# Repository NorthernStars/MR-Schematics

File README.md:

MR-Schematics
============

This repository includes schematic and pcb layout files for some electronical hardware of the Mixed-Reality system.
Cadsoft Eagle (http://www.cadsoftusa.com/?lang=en) is used to generate the these files. Sometimes also a partlist is included.

Included Files
-----
This repository includes files for the following hardware:
* mrShark - Robot mrShark including programmer and debug/charger boards
* IR Testboard - Board for redirecting serial and IR data for debugging
* IR Transmitter - USB Infrared transmitter
* IR Splitter - Splitter for IR system with high current
* LiPo-Charger MultiBoard - Small Robot LiPo chargers that are connectable to any size of charger station
* LiPo-Charger-Station - 3x3 Robot LiPo charger station with microcontroller

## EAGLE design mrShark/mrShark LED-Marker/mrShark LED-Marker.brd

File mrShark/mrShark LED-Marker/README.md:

# mrShark LED-Marker
LEd marker for Mixed-Reality Robotr mrShark.
Includes 3x3 led arry an 4 position lights.
Controlled via I2C/TWI PC9552 led controller.

## PCB Order
Order on 

https://jlcpcb.com/

and upload Gerber File zip.
Dimension of pcb is 26mm x 32mm
    
## Assembly
Place LEDs, ICs and R1, R2, R3 as shown in schematics.
Choose R4 - R11 and R21 corresponding to your LED current (volatge of mrShark is max. 4.1V, average 3.0 - 3.3V, min 2.7V).
Choose R12, R13 for two! LEDs.

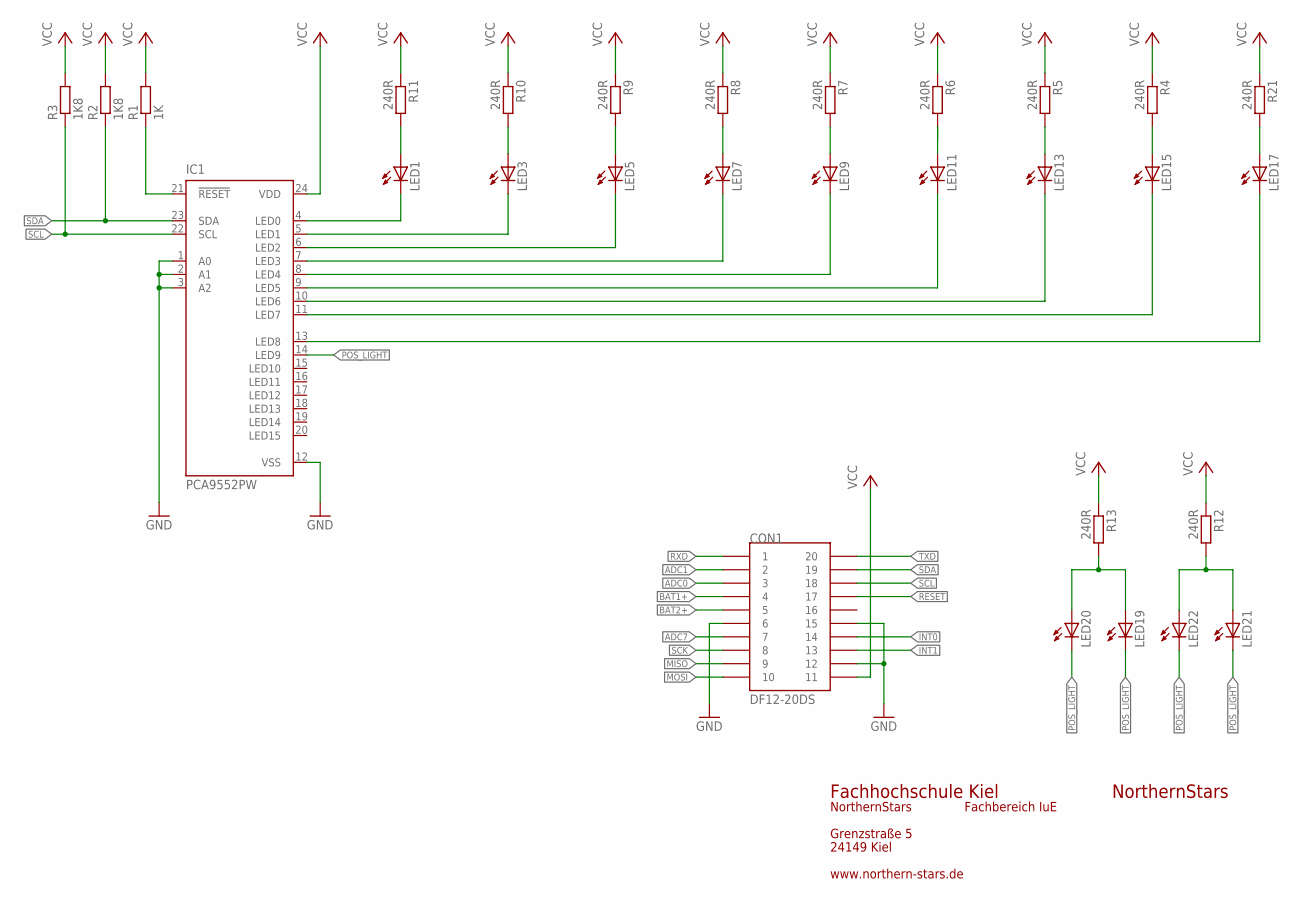
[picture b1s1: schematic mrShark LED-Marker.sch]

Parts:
CON1: DF12-20DS
IC1: PCA9552PW; TSSOP24
LED1, LED3, LED5, LED7, LED9, LED11, LED13, LED15, LED17, LED19, LED20, LED21, LED22: LEDCHIPLED_0603; CHIPLED_0603
R1: 1K; R0603
R2, R3: 1K8; R0603
R4, R5, R6, R7, R8, R9, R10, R11, R12, R13, R21: 240R; R0603

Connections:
ADC0: CON1.3
ADC1: CON1.2
ADC7: CON1.7
BAT1+: CON1.4
BAT2+: CON1.5
GND: CON1.6, CON1.12, CON1.15, IC1.1 (A0), IC1.2 (A1), IC1.3 (A2), IC1.12 (VSS)
INT0: CON1.14
INT1: CON1.13
MISO: CON1.9
MOSI: CON1.10
unnamed: IC1.21 (!RESET), R1.1
unnamed: LED17.A, R21.2
unnamed: LED21.A, LED22.A, R12.2
unnamed: LED15.A, R4.2
unnamed: LED13.A, R5.2
unnamed: LED11.A, R6.2
unnamed: LED9.A, R7.2
unnamed: LED7.A, R8.2
unnamed: LED19.A, LED20.A, R13.2
unnamed: LED5.A, R9.2
unnamed: LED3.A, R10.2
unnamed: LED1.A, R11.2
unnamed: IC1.4 (LED0), LED1.C
unnamed: IC1.5 (LED1), LED3.C
unnamed: IC1.6 (LED2), LED5.C
unnamed: IC1.7 (LED3), LED7.C
unnamed: IC1.8 (LED4), LED9.C
unnamed: IC1.9 (LED5), LED11.C
unnamed: IC1.10 (LED6), LED13.C
unnamed: IC1.11 (LED7), LED15.C
unnamed: IC1.13 (LED8), LED17.C
POS_LIGHT: IC1.14 (LED9), LED19.C, LED20.C, LED21.C, LED22.C
RESET: CON1.17
RXD: CON1.1
SCK: CON1.8
SCL: CON1.18, IC1.22 (SCL), R3.1
SDA: CON1.19, IC1.23 (SDA), R2.1
TXD: CON1.20
VCC: CON1.11, IC1.24 (VDD), R1.2, R2.2, R3.2, R4.1, R5.1, R6.1, R7.1, R8.1, R9.1, R10.1, R11.1, R12.1, R13.1, R21.1

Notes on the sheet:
NorthernStars
Fachhochschule Kiel
Grenzstraße 5
24149 Kiel
Fachbereich IuE
www.northern-stars.de

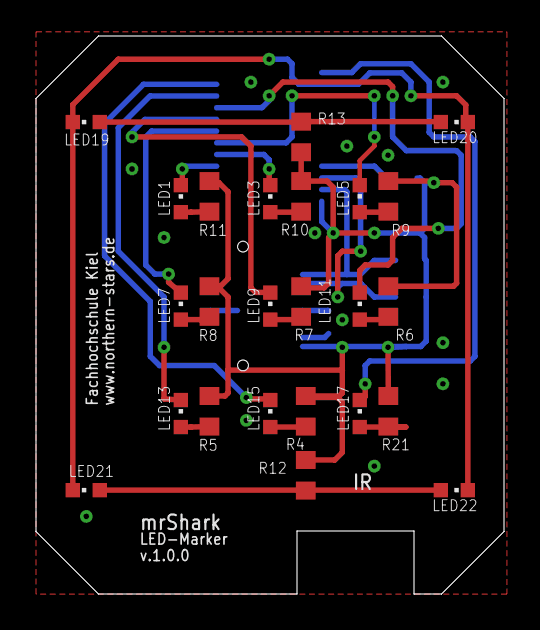
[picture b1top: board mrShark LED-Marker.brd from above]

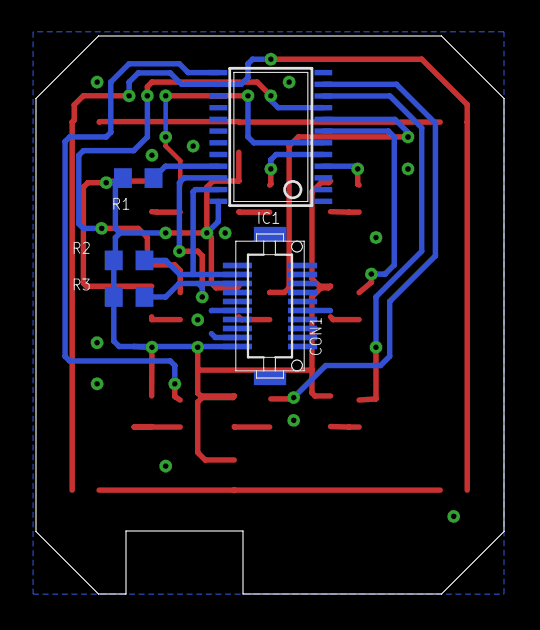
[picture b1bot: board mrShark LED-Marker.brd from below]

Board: 2 copper layers, 26.0 x 31.0 mm, 29 parts (5 on the bottom side), 26 nets.

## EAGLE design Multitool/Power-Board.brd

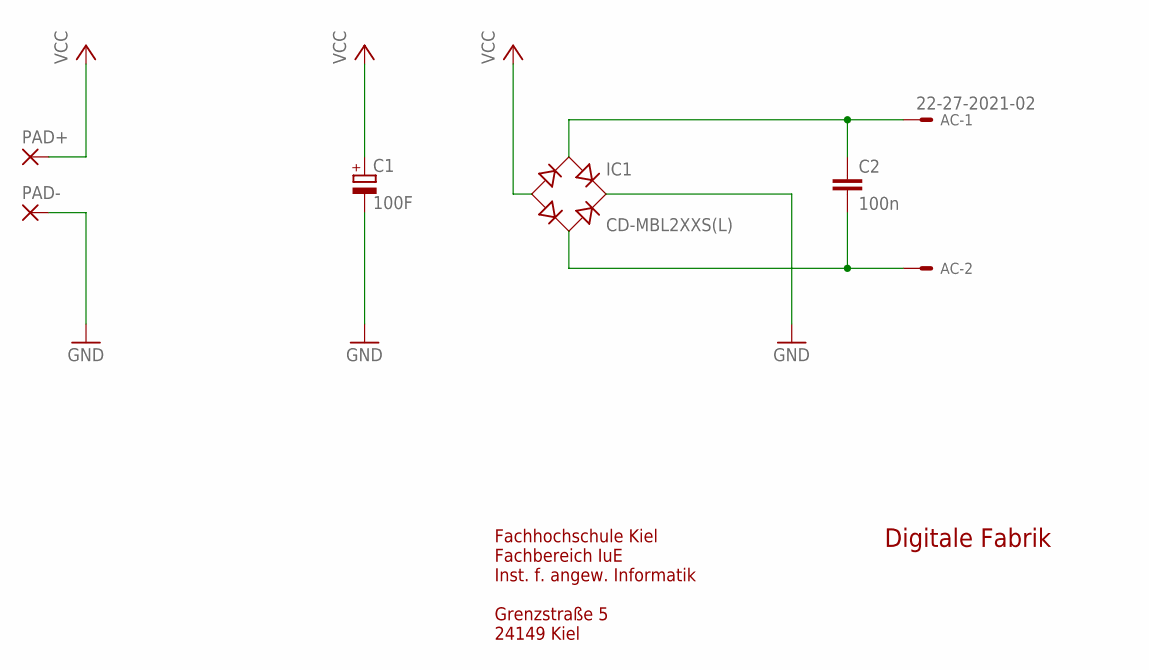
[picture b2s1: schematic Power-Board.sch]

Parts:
AC: 22-27-2021-02; 6410-02
C1: 100F; E7,5-18,5
C2: 100n; C0805K
IC1: CD-MBL2XXS(L)
PAD+: WIREPAD4,16O1,6; 4,16O1,6
PAD-: WIREPAD4,16O1,6; 4,16O1,6

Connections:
GND: C1.-, IC1.DC+ (+), PAD-.1
unnamed: AC.1, C2.1, IC1.AC1
unnamed: AC.2, C2.2, IC1.AC2
VCC: C1.+, IC1.DC- (-), PAD+.1

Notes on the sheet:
Digitale Fabrik
Fachhochschule Kiel Fachbereich IuE Inst. f. angew. Informatik Grenzstraße 5 24149 Kiel

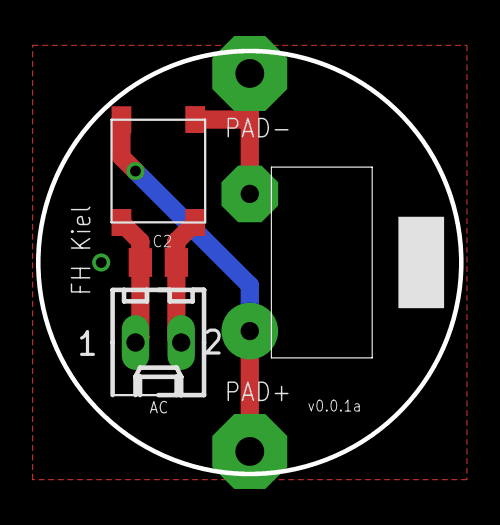
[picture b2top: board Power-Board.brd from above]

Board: 2 copper layers, 23.5 x 23.5 mm, 6 parts (1 on the bottom side), 4 nets.

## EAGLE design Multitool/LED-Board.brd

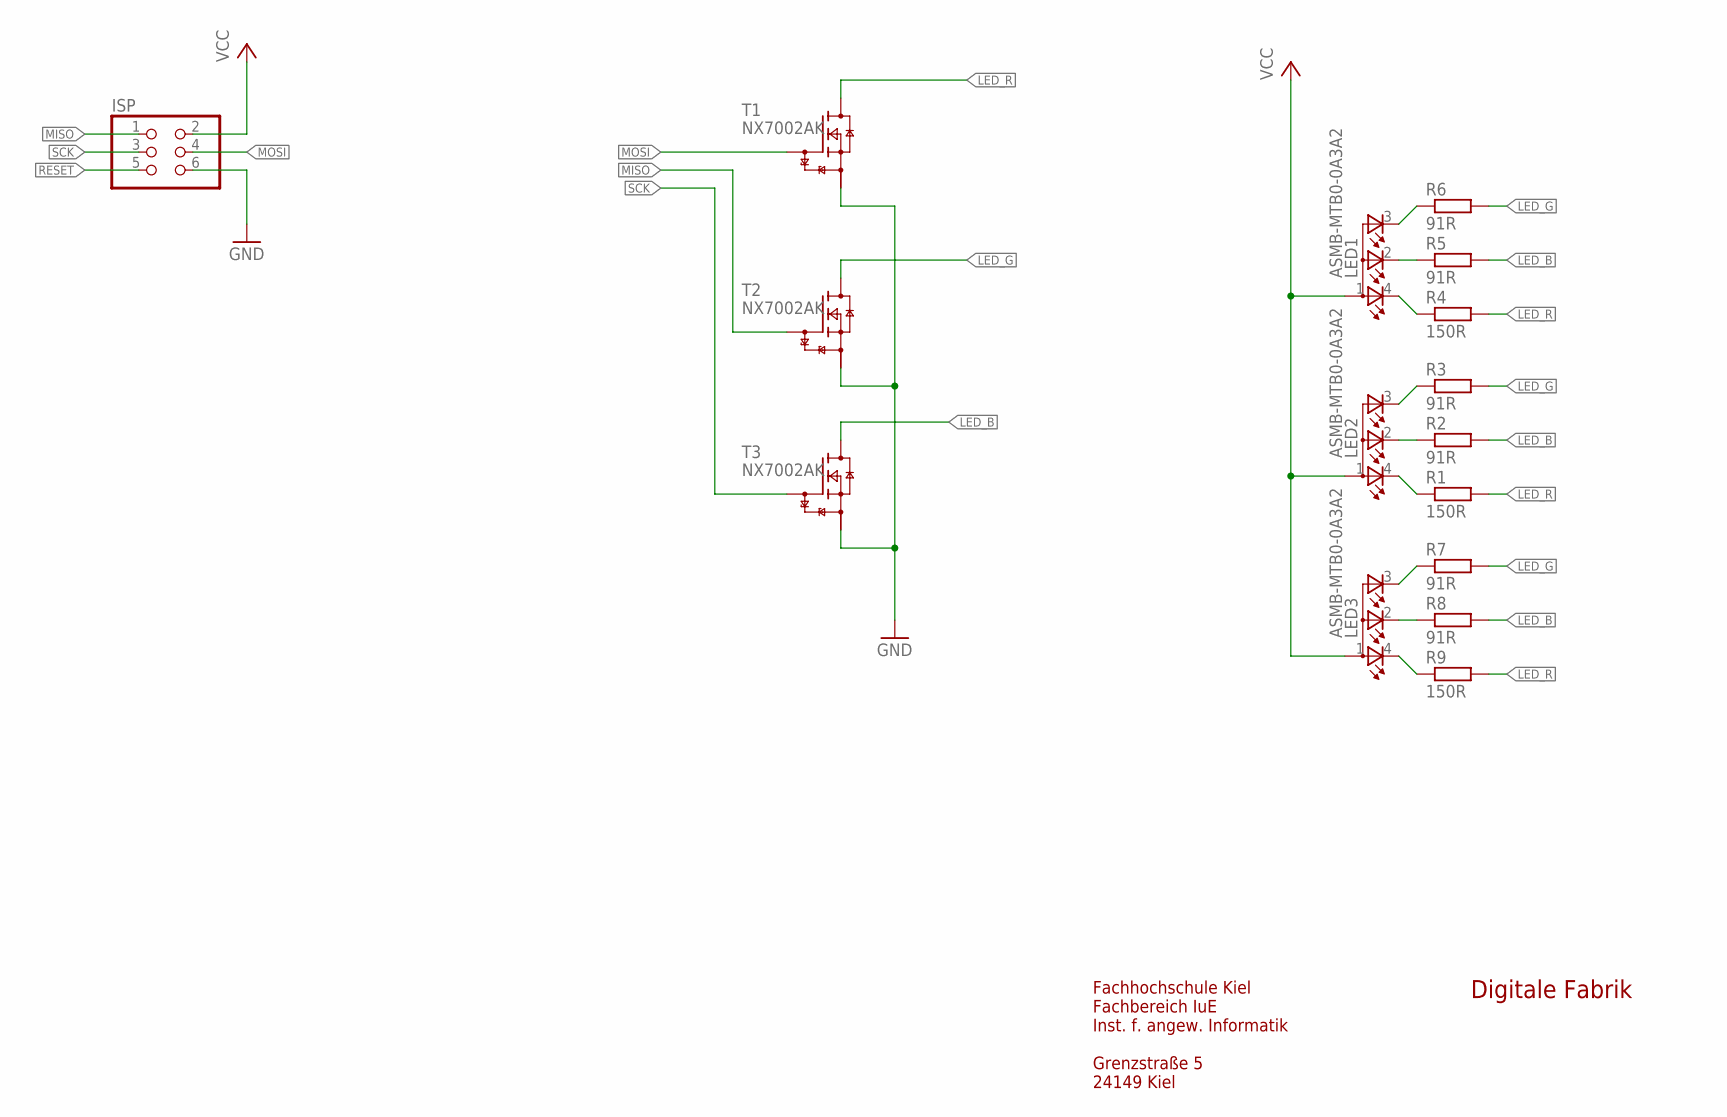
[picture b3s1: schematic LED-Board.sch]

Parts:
ISP: PINHD-2X03_2.54-SMD; 2X03SMD
LED1, LED2, LED3: ASMB-MTB0-0A3A2; P-LCC-4-3
R1, R4, R9: 150R; R0805
R2, R3, R5, R6, R7, R8: 91R; R0805
T1, T2, T3: NX7002AK; SOT23

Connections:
GND: ISP.6, T1.2 (S), T2.2 (S), T3.2 (S)
LED_B: R2.2, R5.2, R8.2, T3.3 (D)
LED_G: R3.2, R6.2, R7.2, T2.3 (D)
LED_R: R1.2, R4.2, R9.2, T1.3 (D)
MISO: ISP.1, T2.1 (G)
MOSI: ISP.4, T1.1 (G)
unnamed: LED1.4 (CRED), R4.1
unnamed: LED1.2 (CBLUE), R5.1
unnamed: LED1.3 (CGREEN), R6.1
unnamed: LED2.4 (CRED), R1.1
unnamed: LED2.2 (CBLUE), R2.1
unnamed: LED2.3 (CGREEN), R3.1
unnamed: LED3.3 (CGREEN), R7.1
unnamed: LED3.2 (CBLUE), R8.1
unnamed: LED3.4 (CRED), R9.1
RESET: ISP.5
SCK: ISP.3, T3.1 (G)
VCC: ISP.2, LED1.1 (A2), LED2.1 (A2), LED3.1 (A2)

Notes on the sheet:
Fachhochschule Kiel Fachbereich IuE Inst. f. angew. Informatik Grenzstraße 5 24149 Kiel
Digitale Fabrik

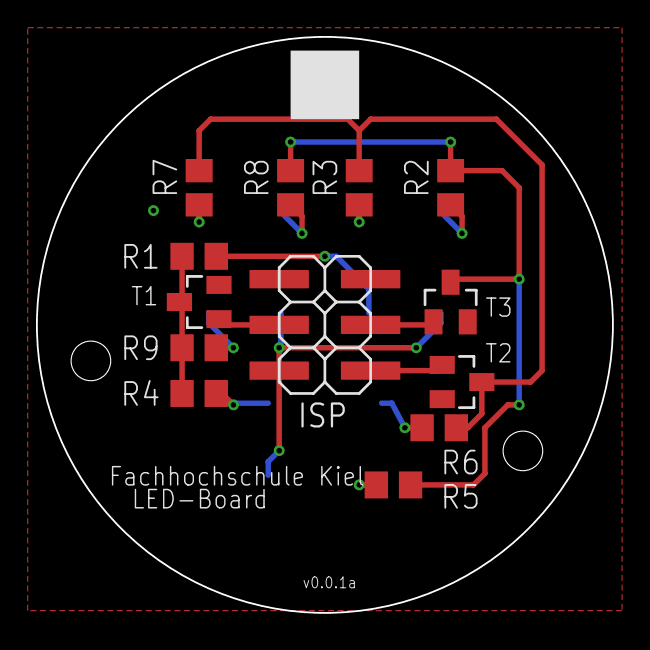
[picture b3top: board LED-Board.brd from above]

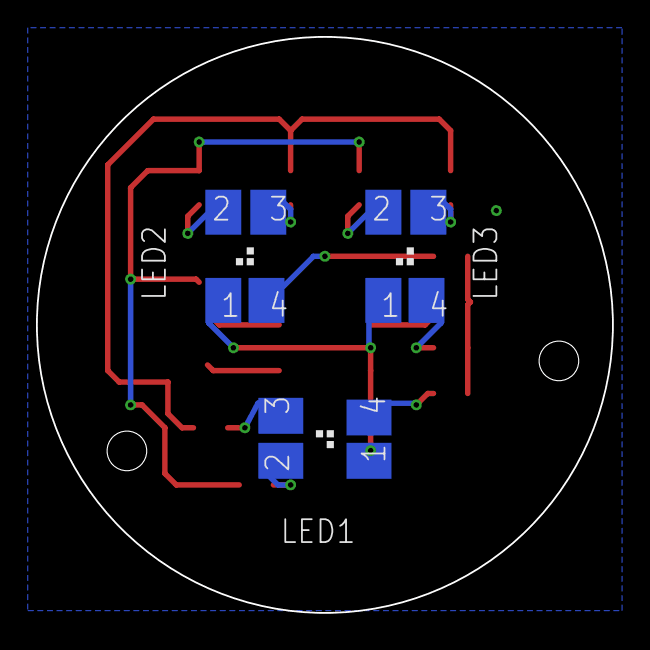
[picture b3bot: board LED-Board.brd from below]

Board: 2 copper layers, 32.0 x 32.0 mm, 16 parts (3 on the bottom side), 17 nets.

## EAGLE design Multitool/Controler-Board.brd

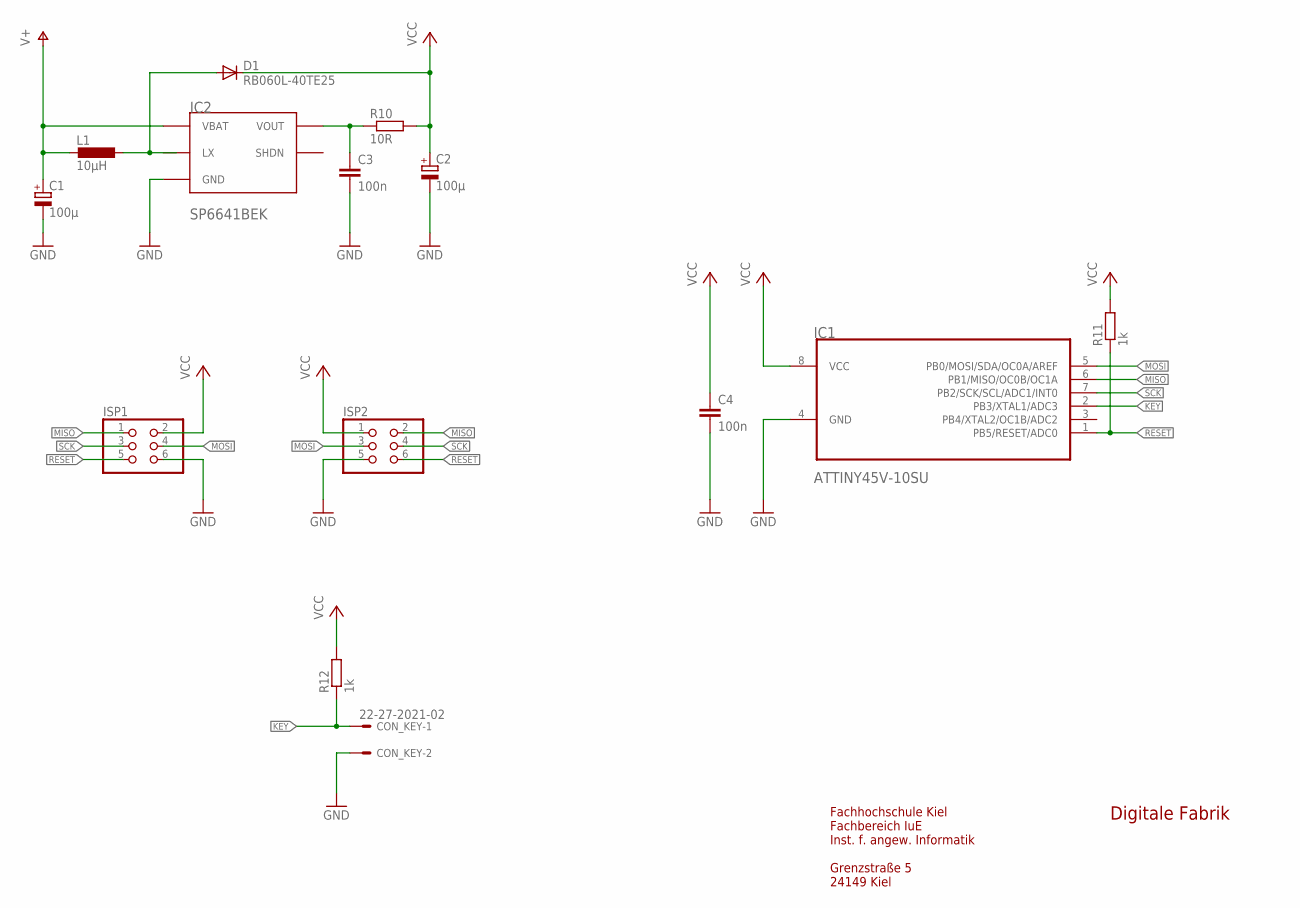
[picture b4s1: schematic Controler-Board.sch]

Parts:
C1, C2: 100µ; PANASONIC_C
C3: 100n; C1206
C4: 100n; C0805
CON_KEY: 22-27-2021-02; 6410-02
D1: RB060L-40TE25; SOD106-R
IC1: ATTINY45V-10SU; SOIC127P798X216-8N
IC2: SP6641BEK; SOT23-5
ISP1, ISP2: PINHD-2X03_2.54-SMD; 2X03SMD
L1: 10µH; R1206
R10: 10R; R0805
R11, R12: 1k; R0805

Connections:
GND: C1.-, C2.-, C3.2, C4.2, CON_KEY.2, IC1.4 (GND), IC2.2 (GND), ISP1.6, ISP2.5
KEY: CON_KEY.1, IC1.2 (PB3/XTAL1/ADC3), R12.1
MISO: IC1.6 (PB1/MISO/OC0B/OC1A), ISP1.1, ISP2.2
MOSI: IC1.5 (PB0/MOSI/SDA/OC0A/AREF), ISP1.4, ISP2.3
unnamed: C3.1, IC2.3 (VOUT), R10.1
unnamed: D1.A, L1.1
RESET: IC1.1 (PB5/RESET/ADC0), ISP1.5, ISP2.6, R11.1
SCK: IC1.7 (PB2/SCK/SCL/ADC1/INT0), ISP1.3, ISP2.4
V+: C1.+, IC2.5 (VBAT), L1.2
VCC: C2.+, C4.1, D1.C, IC1.8 (VCC), ISP1.2, ISP2.1, R10.2, R11.2, R12.2

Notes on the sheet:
Fachhochschule Kiel Fachbereich IuE Inst. f. angew. Informatik Grenzstraße 5 24149 Kiel
Digitale Fabrik

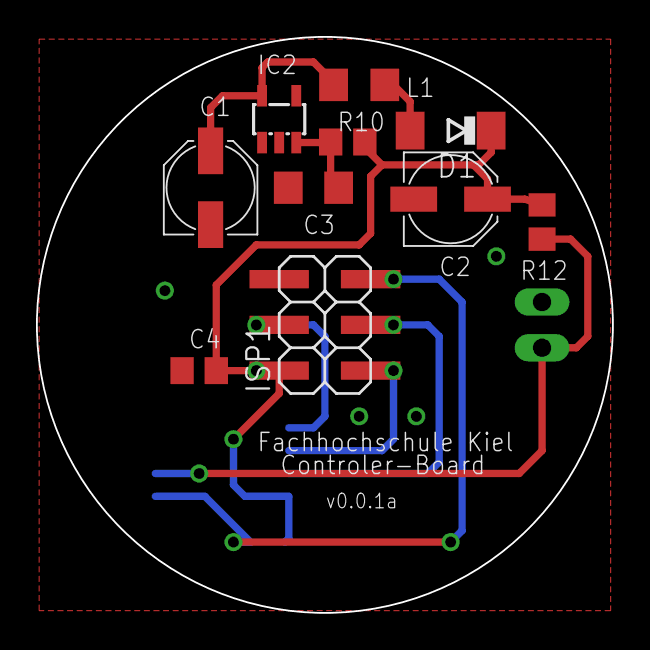
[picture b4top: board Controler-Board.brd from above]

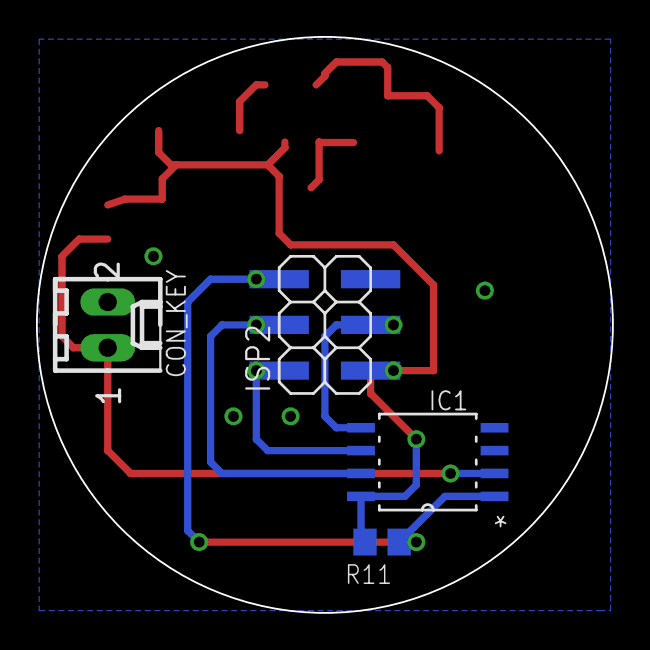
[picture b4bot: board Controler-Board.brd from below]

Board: 2 copper layers, 32.0 x 32.0 mm, 14 parts (4 on the bottom side), 10 nets.

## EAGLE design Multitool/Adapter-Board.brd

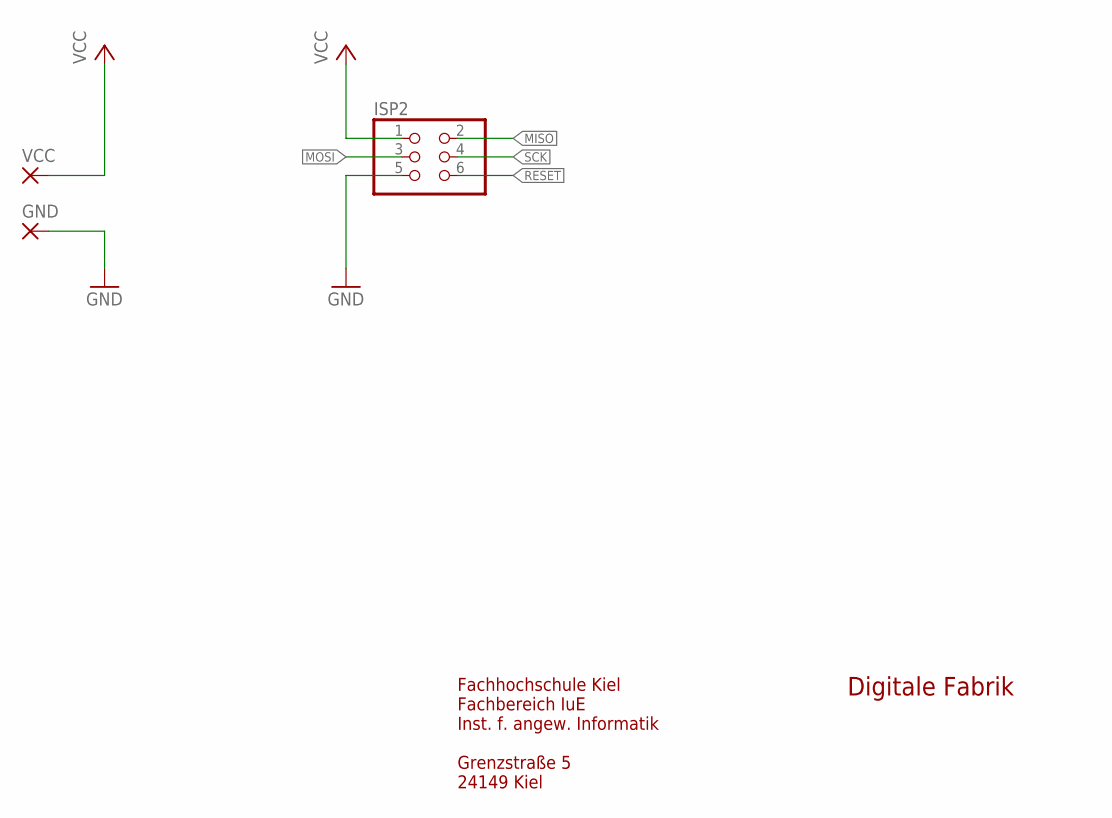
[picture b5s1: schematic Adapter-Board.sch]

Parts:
GND: SMD5; SMD2,54-5,08
ISP2: PINHD-2X03_2.54-SMD; 2X03SMD
VCC: SMD5; SMD2,54-5,08

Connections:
GND: GND.1, ISP2.5
MISO: ISP2.2
MOSI: ISP2.3
RESET: ISP2.6
SCK: ISP2.4
VCC: ISP2.1, VCC.1

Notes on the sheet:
Fachhochschule Kiel Fachbereich IuE Inst. f. angew. Informatik Grenzstraße 5 24149 Kiel
Digitale Fabrik

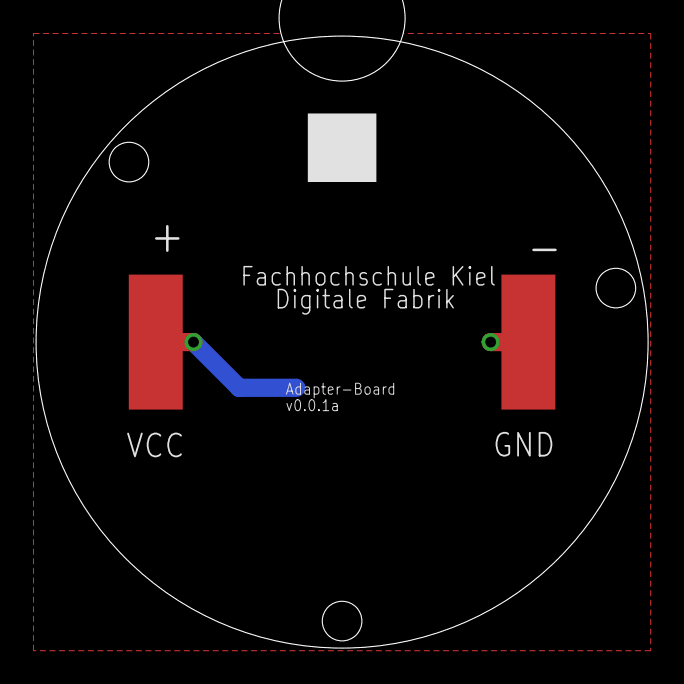
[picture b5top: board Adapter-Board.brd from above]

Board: 2 copper layers, 34.0 x 34.0 mm, 3 parts (1 on the bottom side), 2 nets.

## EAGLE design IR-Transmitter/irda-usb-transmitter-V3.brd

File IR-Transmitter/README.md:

IR-Transmitter
==============
Use this infrared transmitter to send commands data to the Mixed-Reality robots.
The boeard has a USB connector with and FTDI USB-to-Serial converter so you can plug this board directly into you computer.
The board uses a 115.2kbit/s transmission rate for sending infrared data.

Add a power supply to V+ and GND. You can add any power supply from 5V to 12V (7.5V is recommended).
Add some infrared leds to the LED+ and LED- pads.

You can use the jumper JP1 to use the USB 5V bus power to get a portable IR-Transmitter.
Take care that the maximum output current of the USB bus is 500mA.
If you add ~4 IR-LEDs it should work.

For small mobile IR-Transmitter select a suitable resistor for R2 and don't assemble R3.

Be aware that this board isn't build for high currents!
For that use the IR-Splitter. Maybe you also should use a heatsink on the MOSFET.
To do so, bridge resistor R2 and use 1k ohm resistor for R3. Connect IR data signal for IR-Splitter to LED- and GND of IR-Splitter to GND.

Order
-----
You can order this transmitter via www.dirtypcbs.com
* http://dirtypcbs.com/view.php?share=3876&accesskey=a4be5c8c025c9f4713186b7ca5dc06cf

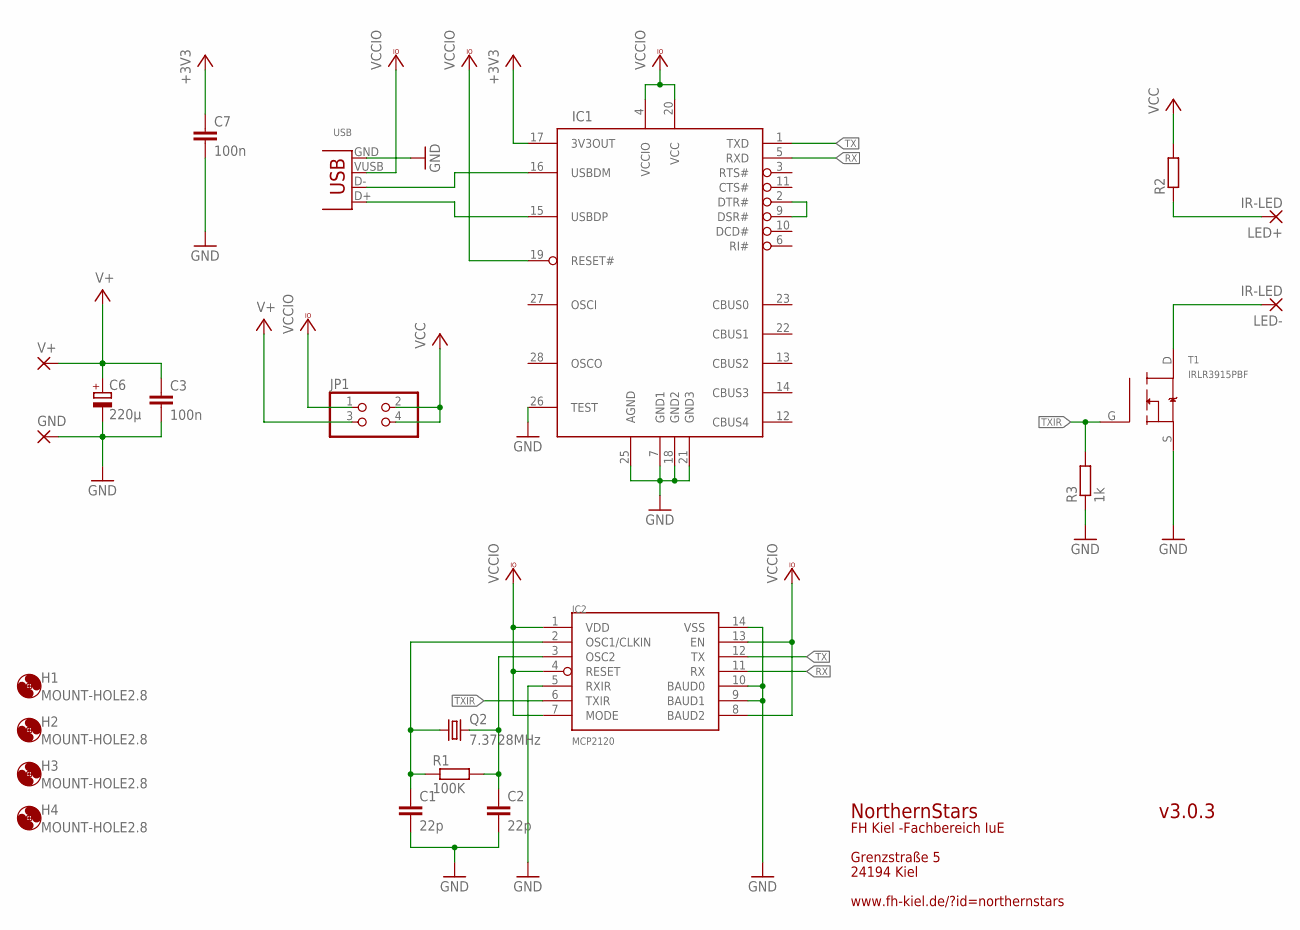
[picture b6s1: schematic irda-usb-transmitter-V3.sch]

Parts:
C1, C2: 22p; C0805
C3, C7: 100n; C1206
C6: 220µ; E3,5-8
GND: SMD5; SMD2,54-5,08
H1, H2, H3, H4: MOUNT-HOLE2.8; 2,8
IC1: FT232RL; SSOP28DB
IC2: MCP2120; SO-14
JP1: PINHD-2X2; 2X02
LED+: IR-LED; 5-2,5
LED-: IR-LED; 5-2,5
Q2: 7.3728MHz; HC49UP
R1: 100K; R1206
R2: R-EU_R1206; R1206
R3: 1k; R1206
T1: IRLR3915PBF; D-PAK
USB: USB-B-S; USB-B-SMT
V+: SMD5; SMD2,54-5,08

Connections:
+3V3: C7.1, IC1.17 (3V3OUT)
D+: IC1.15 (USBDP), USB.D+
D-: IC1.16 (USBDM), USB.D-
GND: C1.2, C2.2, C3.2, C6.-, C7.2, GND.1, IC1.7 (GND1), IC1.18 (GND2), IC1.21 (GND3), IC1.25 (AGND), IC1.26 (TEST), IC2.5 (RXIR), IC2.9 (BAUD1), IC2.10 (BAUD0), IC2.14 (VSS), R3.1, T1.S, USB.GND
IRLEDS-: LED-.1, T1.D
unnamed: LED+.1, R2.1
unnamed: IC1.2 (DTR#), IC1.9 (DSR#)
unnamed: C1.1, IC2.2 (OSC1/CLKIN), Q2.1, R1.1
unnamed: C2.1, IC2.3 (OSC2), Q2.2, R1.2
RX: IC1.5 (RXD), IC2.11 (RX)
TX: IC1.1 (TXD), IC2.12 (TX)
TXIR: IC2.6 (TXIR), R3.2, T1.G
V+: C3.1, C6.+, JP1.3, V+.1
VCC: JP1.2, JP1.4, R2.2
VCCIO: IC1.4 (VCCIO), IC1.19 (RESET#), IC1.20 (VCC), IC2.1 (VDD), IC2.4 (RESET), IC2.7 (MODE), IC2.8 (BAUD2), IC2.13 (EN), JP1.1, USB.VUSB (VBUS)

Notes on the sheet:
v3.0.3
NorthernStars
FH Kiel -Fachbereich IuE
Grenzstraße 5
24194 Kiel
www.fh-kiel.de/?id=northernstars

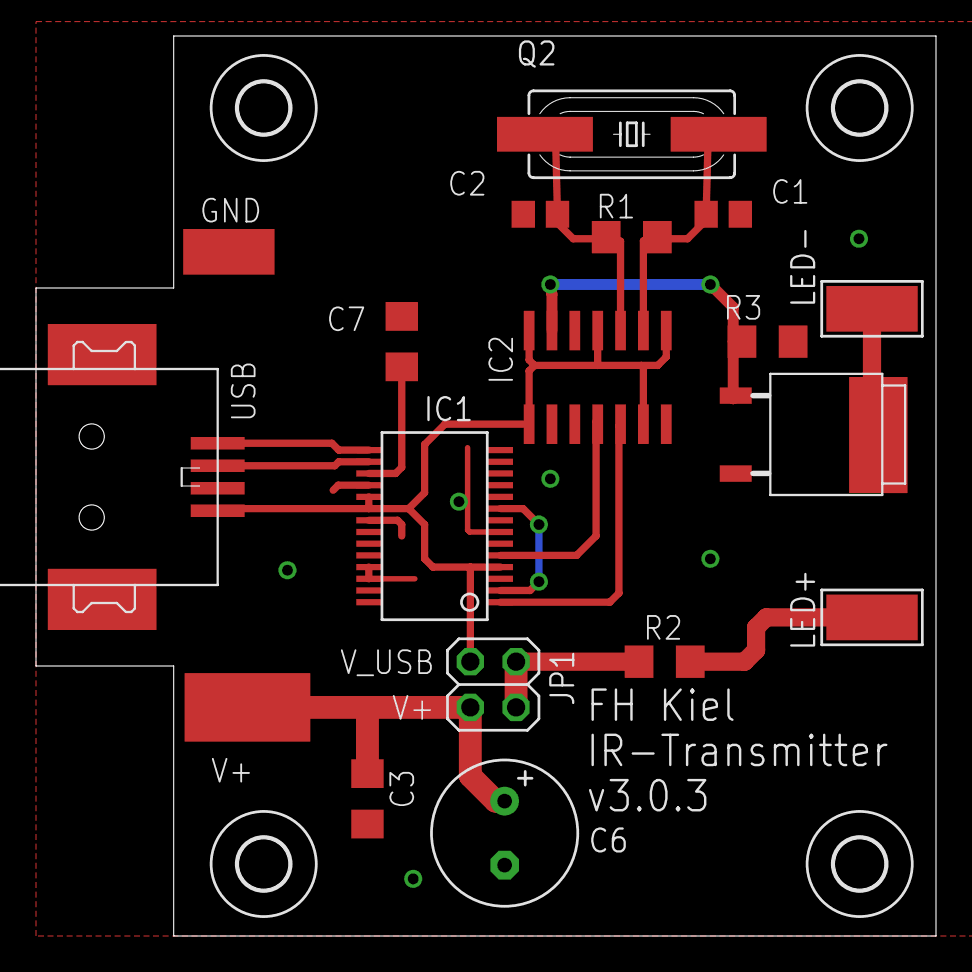
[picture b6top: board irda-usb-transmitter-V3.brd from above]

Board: 2 copper layers, 50.0 x 50.0 mm, 22 parts (0 on the bottom side), 15 nets.

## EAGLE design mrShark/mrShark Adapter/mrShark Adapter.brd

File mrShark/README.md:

mrShark
=======
Here you find schemtics and board layout needed for the Mixed-Relality Robot mrShark.
The main board is the mrShark controlling everything on the robot.
For programming you also need the programmer board. Optional you can use the debuger board to charge the robots batteries and use the serial debug interface to test the robot without infrared communication.

## What you need

* mrShark (main controller board, always use latest version)
* LED-Marker (vision detection marker) 
* mrShark Adapter (programming, debugging and charging)

Also consider using the LiPo-Charger-Multiboard for charging larger sets of robots.

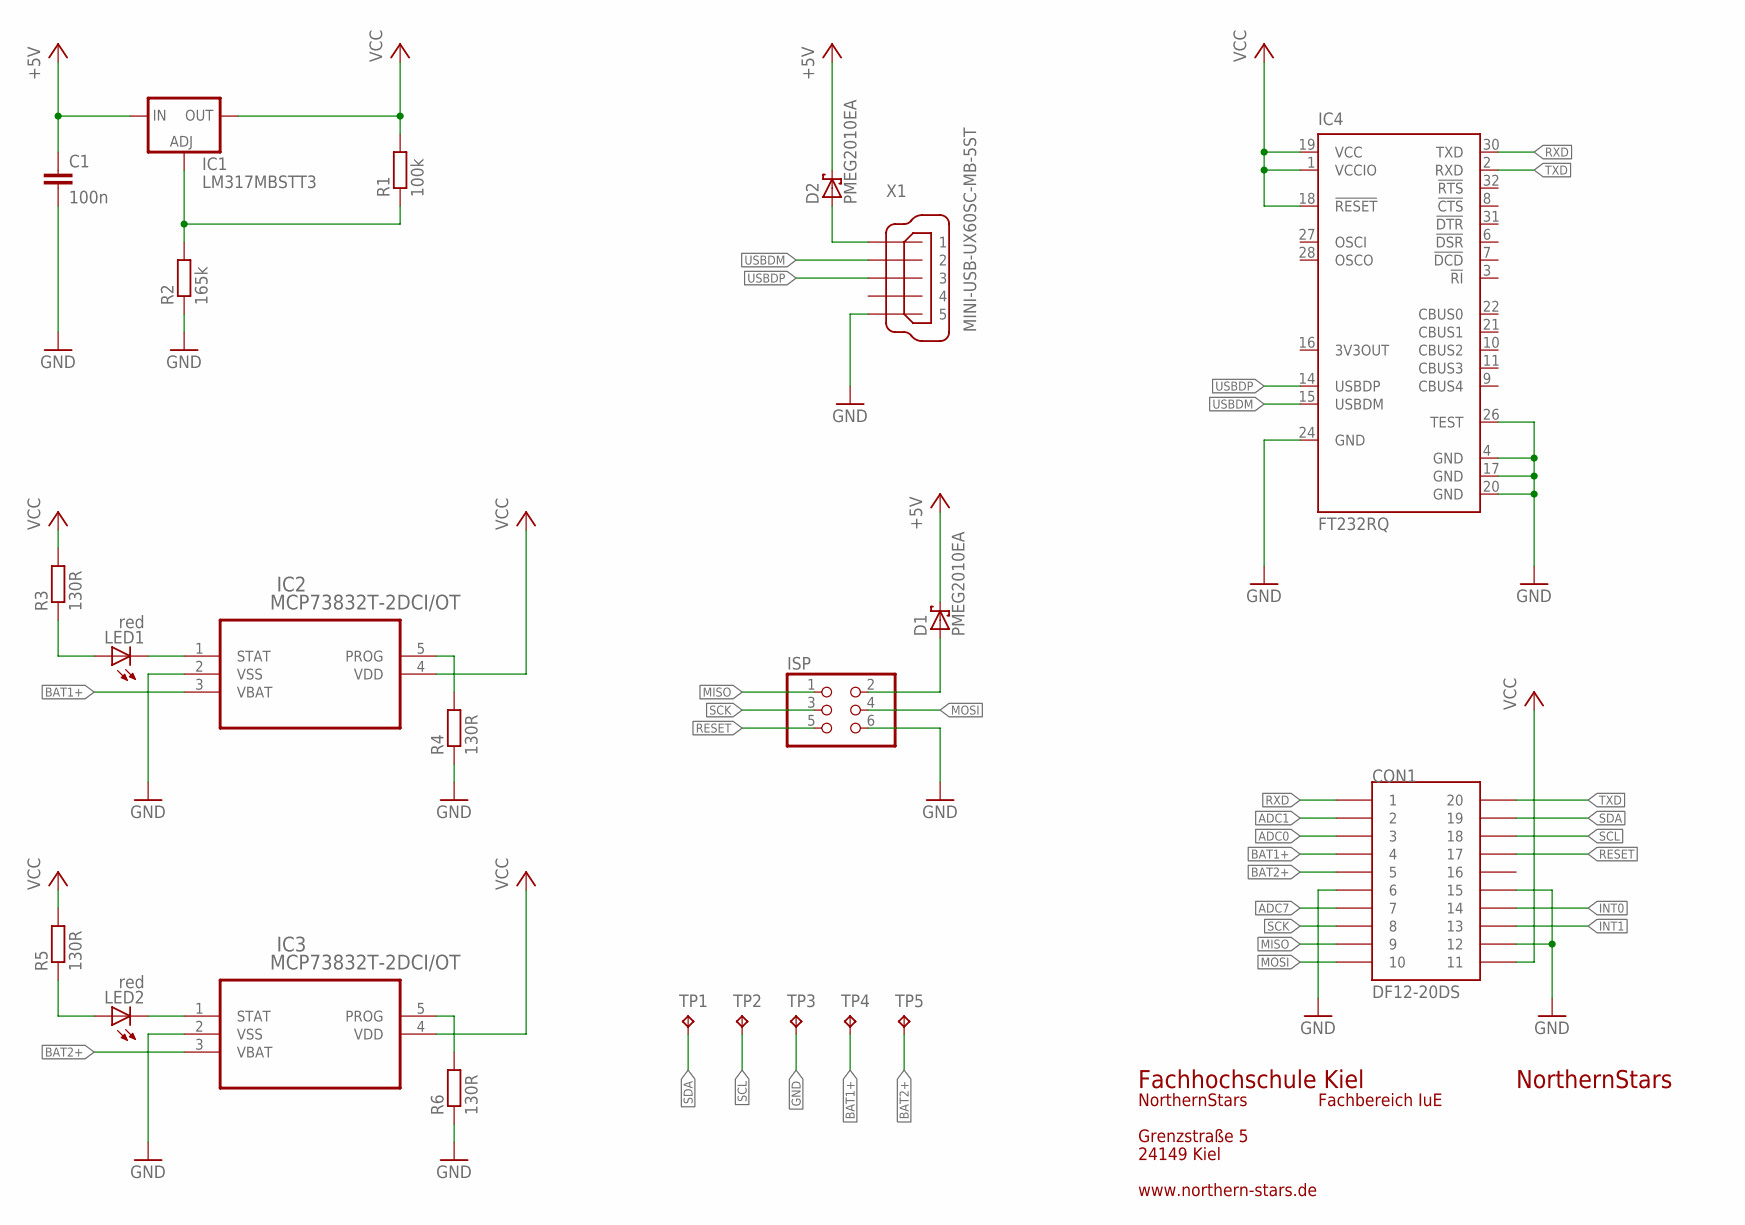
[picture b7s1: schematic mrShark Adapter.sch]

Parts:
C1: 100n; C0603
CON1: DF12-20DS
D1, D2: PMEG2010EA; SOD323-R
IC1: LM317MBSTT3; SOT223
IC2, IC3: MCP73832T-2DCI/OT; SOT95P300X145-5N
IC4: FT232RQ; QFN32
ISP: PINHD-2X03_2.54-SMD; 2X03SMD
LED1, LED2: red; CHIP-LED0603
R1: 100k; R0603
R2: 165k; R0603
R3, R4, R5, R6: 130R; R0603
TP1, TP2, TP3, TP4, TP5: TPTP06SQ; TP06SQ
X1: MINI-USB-UX60SC-MB-5ST; UX60SC-MB-5ST

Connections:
+5V: C1.1, D1.C, D2.C, IC1.3 (IN)
ADC0: CON1.3
ADC1: CON1.2
ADC7: CON1.7
BAT1+: CON1.4, IC2.3 (VBAT), TP4.TP
BAT2+: CON1.5, IC3.3 (VBAT), TP5.TP
GND: C1.2, CON1.6, CON1.12, CON1.15, IC2.2 (VSS), IC3.2 (VSS), IC4.4 (GND), IC4.17 (GND), IC4.20 (GND), IC4.24 (GND), IC4.26 (TEST), ISP.6, R2.1, R4.1, R6.1, TP3.TP, X1.5
INT0: CON1.14
INT1: CON1.13
MISO: CON1.9, ISP.1
MOSI: CON1.10, ISP.4
unnamed: IC1.1 (ADJ), R1.1, R2.2
unnamed: IC2.1 (STAT), LED1.C
unnamed: LED1.A, R3.1
unnamed: D1.A, ISP.2
unnamed: IC2.5 (PROG), R4.2
unnamed: LED2.A, R5.1
unnamed: IC3.1 (STAT), LED2.C
unnamed: IC3.5 (PROG), R6.2
unnamed: D2.A, X1.1
RESET: CON1.17, ISP.5
RXD: CON1.1, IC4.30 (TXD)
SCK: CON1.8, ISP.3
SCL: CON1.18, TP2.TP
SDA: CON1.19, TP1.TP
TXD: CON1.20, IC4.2 (RXD)
USBDM: IC4.15 (USBDM), X1.2
USBDP: IC4.14 (USBDP), X1.3
VCC: CON1.11, IC1.4 (OUT), IC2.4 (VDD), IC3.4 (VDD), IC4.1 (VCCIO), IC4.18 (!RESET), IC4.19 (VCC), R1.2, R3.2, R5.2

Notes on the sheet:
NorthernStars
Fachhochschule Kiel
Grenzstraße 5
24149 Kiel
Fachbereich IuE
www.northern-stars.de

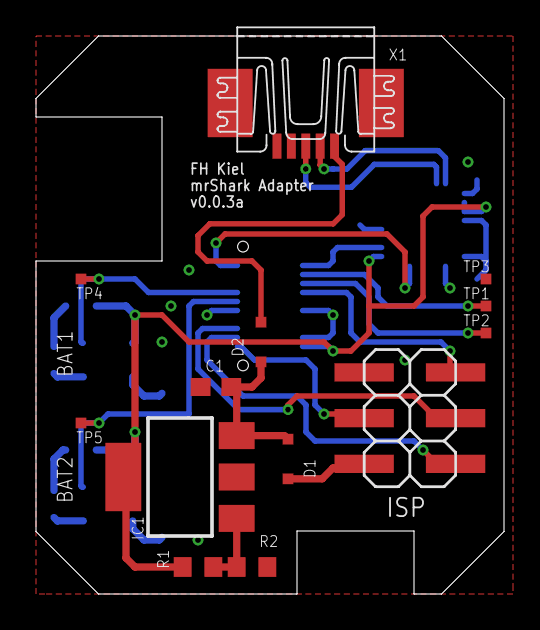
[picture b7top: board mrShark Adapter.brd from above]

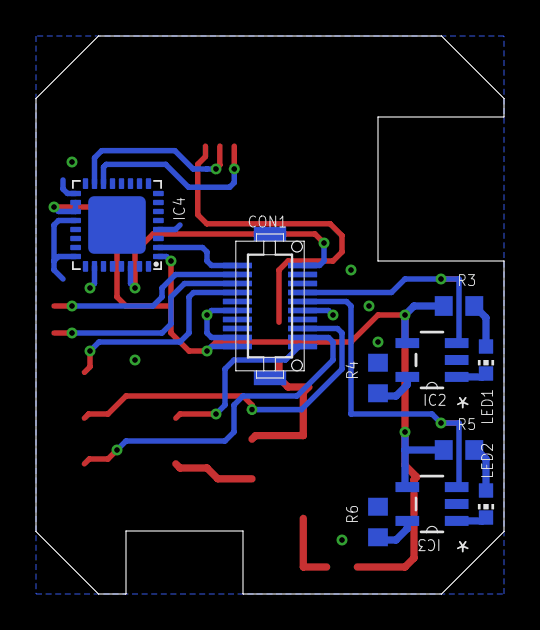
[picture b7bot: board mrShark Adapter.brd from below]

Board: 2 copper layers, 26.0 x 31.0 mm, 23 parts (10 on the bottom side), 24 nets.

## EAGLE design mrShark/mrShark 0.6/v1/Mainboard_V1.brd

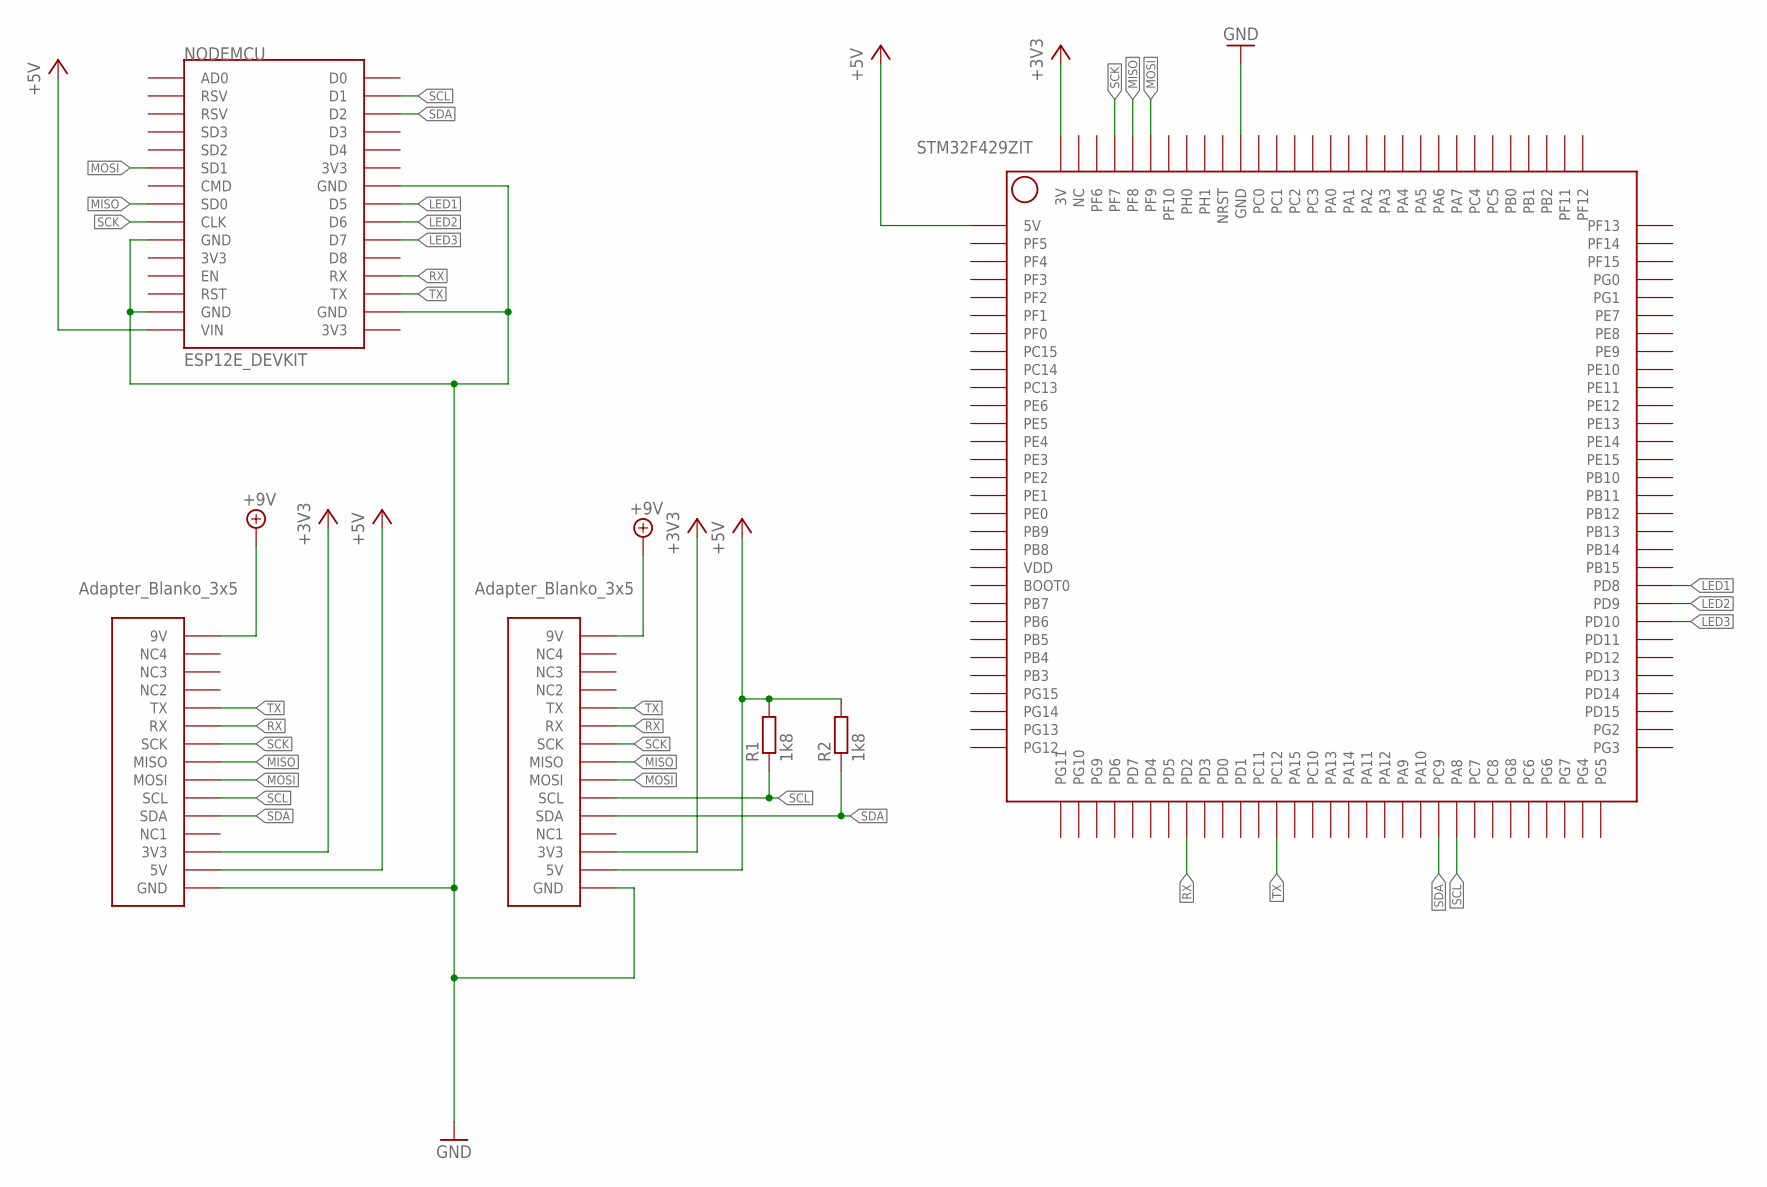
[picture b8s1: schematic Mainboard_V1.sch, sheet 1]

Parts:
NODEMCU: ESP12E_DEVKIT
R1, R2: 1k8; R0805
U$1: STM32F429ZIT
U$2, U$3: ADAPTER_BLANKO_3X5B1; ADAPTER_BLANKO_3X5_B1

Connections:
+3V3: U$1.3V, U$1.3V1 (3V), U$2.3V3, U$2.3V3_1 (3V3), U$3.3V3, U$3.3V3_1 (3V3); also elsewhere on the board
+5V: NODEMCU.VIN, R1.2, R2.2, U$1.5V, U$1.5V1 (5V), U$2.5V, U$2.5V_1 (5V), U$3.5V, U$3.5V_1 (5V); also elsewhere on the board
+9V: U$2.9V, U$2.9V_1 (9V), U$3.9V, U$3.9V_1 (9V); also elsewhere on the board
GND: NODEMCU.GND@0 (GND), NODEMCU.GND@1 (GND), NODEMCU.GND@2 (GND), NODEMCU.GND@3 (GND), U$1.GND, U$1.GND1 (GND), U$1.GND2 (GND), U$1.GND3 (GND), U$1.GND4 (GND), U$1.GND5 (GND), U$2.GND, U$2.GND1 (GND), U$2.GND2 (GND), U$2.GND3 (GND), U$3.GND, U$3.GND1 (GND), U$3.GND2 (GND), U$3.GND3 (GND); also elsewhere on the board
LED1: NODEMCU.D5, U$1.PD8; also elsewhere on the board
LED2: NODEMCU.D6, U$1.PD9; also elsewhere on the board
LED3: NODEMCU.D7, U$1.PD10; also elsewhere on the board
MISO: NODEMCU.SD0, U$1.PF8, U$2.MISO, U$2.MISO_1 (MISO), U$3.MISO, U$3.MISO_1 (MISO)
MOSI: NODEMCU.SD1, U$1.PF9, U$2.MOSI, U$2.MOSI_1 (MOSI), U$3.MOSI, U$3.MOSI_1 (MOSI)
RX: NODEMCU.RX, U$1.PD2, U$2.RX, U$2.RX_1 (RX), U$3.RX, U$3.RX_1 (RX)
SCK: NODEMCU.CLK, U$1.PF7, U$2.SCK, U$2.SCK_1 (SCK), U$3.SCK, U$3.SCK_1 (SCK)
SCL: NODEMCU.D1, R1.1, U$1.PA8, U$2.SCL, U$2.SCL_1 (SCL), U$3.SCL, U$3.SCL_1 (SCL)
SDA: NODEMCU.D2, R2.1, U$1.PC9, U$2.SDA, U$2.SDA_1 (SDA), U$3.SDA, U$3.SDA_1 (SDA)
TX: NODEMCU.TX, U$1.PC12, U$2.TX, U$2.TX_1 (TX), U$3.TX, U$3.TX_1 (TX)
